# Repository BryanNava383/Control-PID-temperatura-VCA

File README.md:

# Control-PID-temperatura-VCA
Control de potencia de un circuito AC luminoso, para regular temperatura

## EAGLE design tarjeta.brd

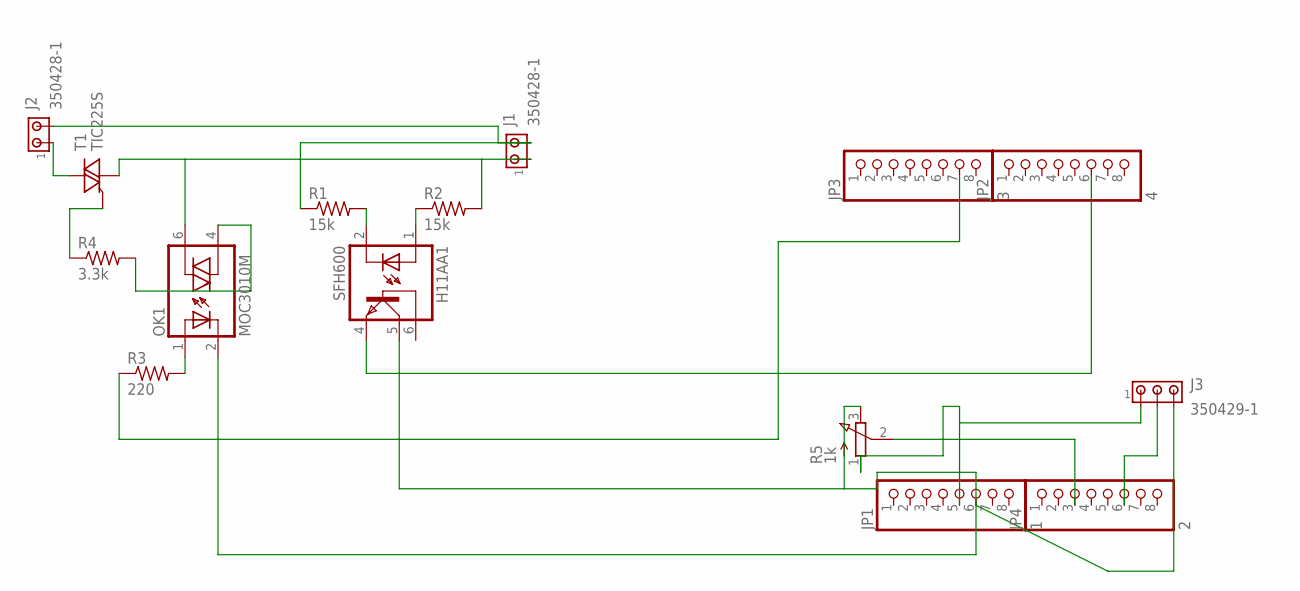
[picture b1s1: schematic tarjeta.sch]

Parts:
H11AA1: SFH600; DIL06
J1, J2: 350428-1
J3: 350429-1
JP1: 1; 1X08/90
JP2: 4; 1X08/90
JP3: 3; 1X08/90
JP4: 2; 1X08/90
OK1: MOC3010M; DIL06
R1, R2: 15k; 0207/10
R3: 220; 0207/10
R4: 3.3k; 0207/10
R5: 1k; 3RP/1610N
T1: TIC225S; TO220DS

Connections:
5V: J3.1, JP1.5, R5.1 (A)
110V: J1.1, OK1.6 (A2), R2.2, T1.A1
GND: H11AA1.5 (COL), J3.3, JP1.6, OK1.2 (C), R5.3 (E)
unnamed: JP3.7, R3.1
unnamed: OK1.4 (A1), R4.2
unnamed: J2.1, T1.A2
unnamed: H11AA1.1 (A), R2.1
unnamed: H11AA1.2 (C), R1.2
unnamed: R4.1, T1.G
unnamed: OK1.1 (A), R3.2
unnamed: H11AA1.4 (EMI), JP2.6
NEUTRO: J1.2, J2.2, R1.1
POTENCIOMETRO: JP4.3, R5.2 (S)
SENSOR: J3.2, JP4.6

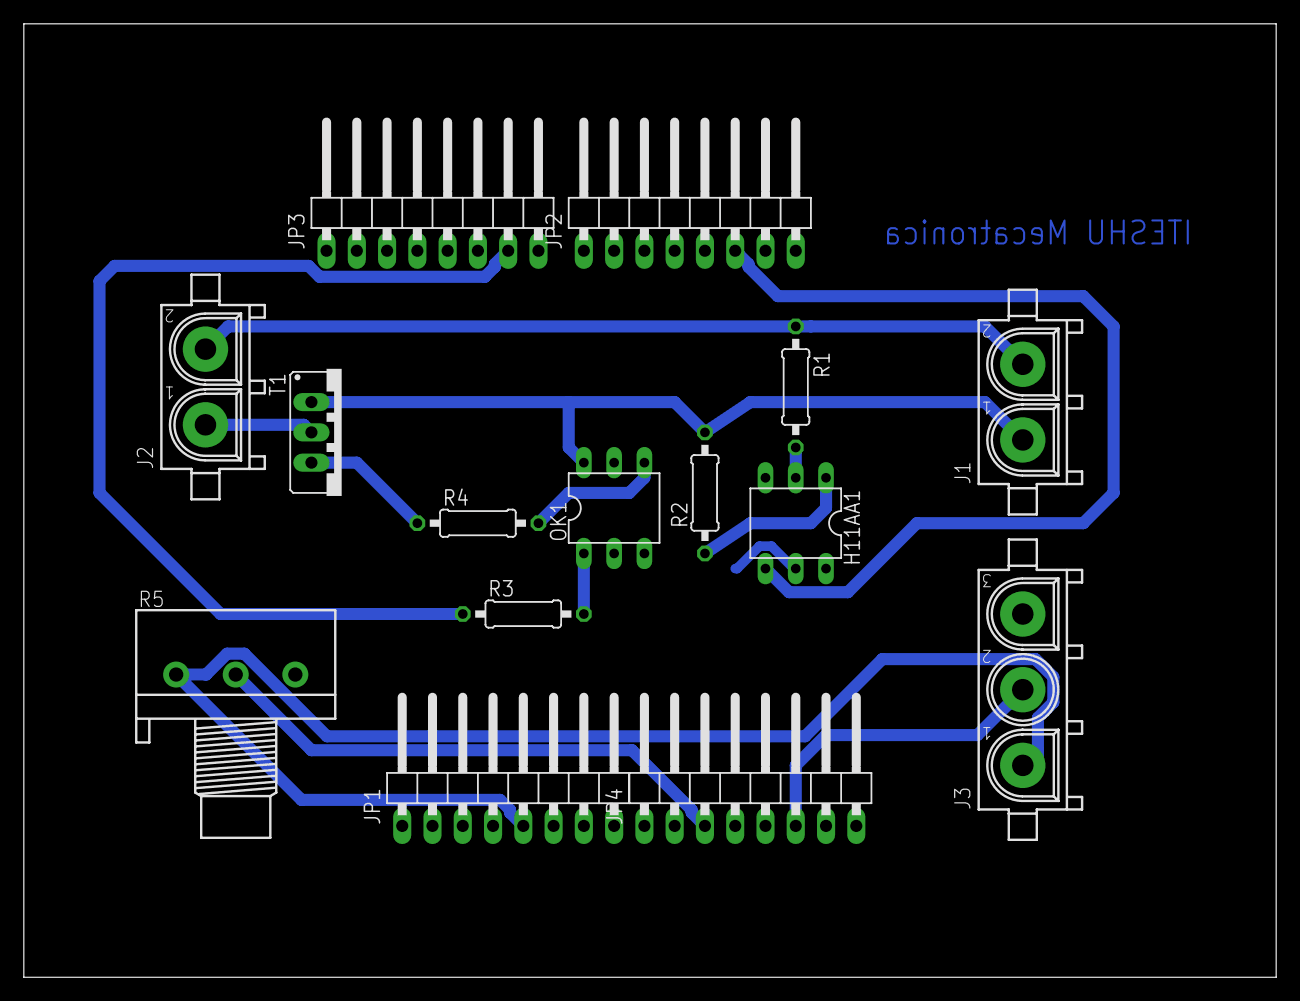
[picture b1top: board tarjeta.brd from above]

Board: 2 copper layers, 105.1 x 80.0 mm, 15 parts (0 on the bottom side), 14 nets.
